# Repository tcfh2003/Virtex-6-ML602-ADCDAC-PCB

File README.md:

# ADC/DAC FPGA Mezannine Card utilizing VITA 57.1 compliant LPC connector.

ADC used is ADC10D040CIVS and has two 10-bit 40 MSa/s channels. DAC used is DAC5652 and has two 10-bit 200 MSa/s channels. 

You can view the PCB online by using https://kicanvas.org (made by theacodes, project github link https://github.com/theacodes/kicanvas.git), and providing the link for the .pro file in this repo.

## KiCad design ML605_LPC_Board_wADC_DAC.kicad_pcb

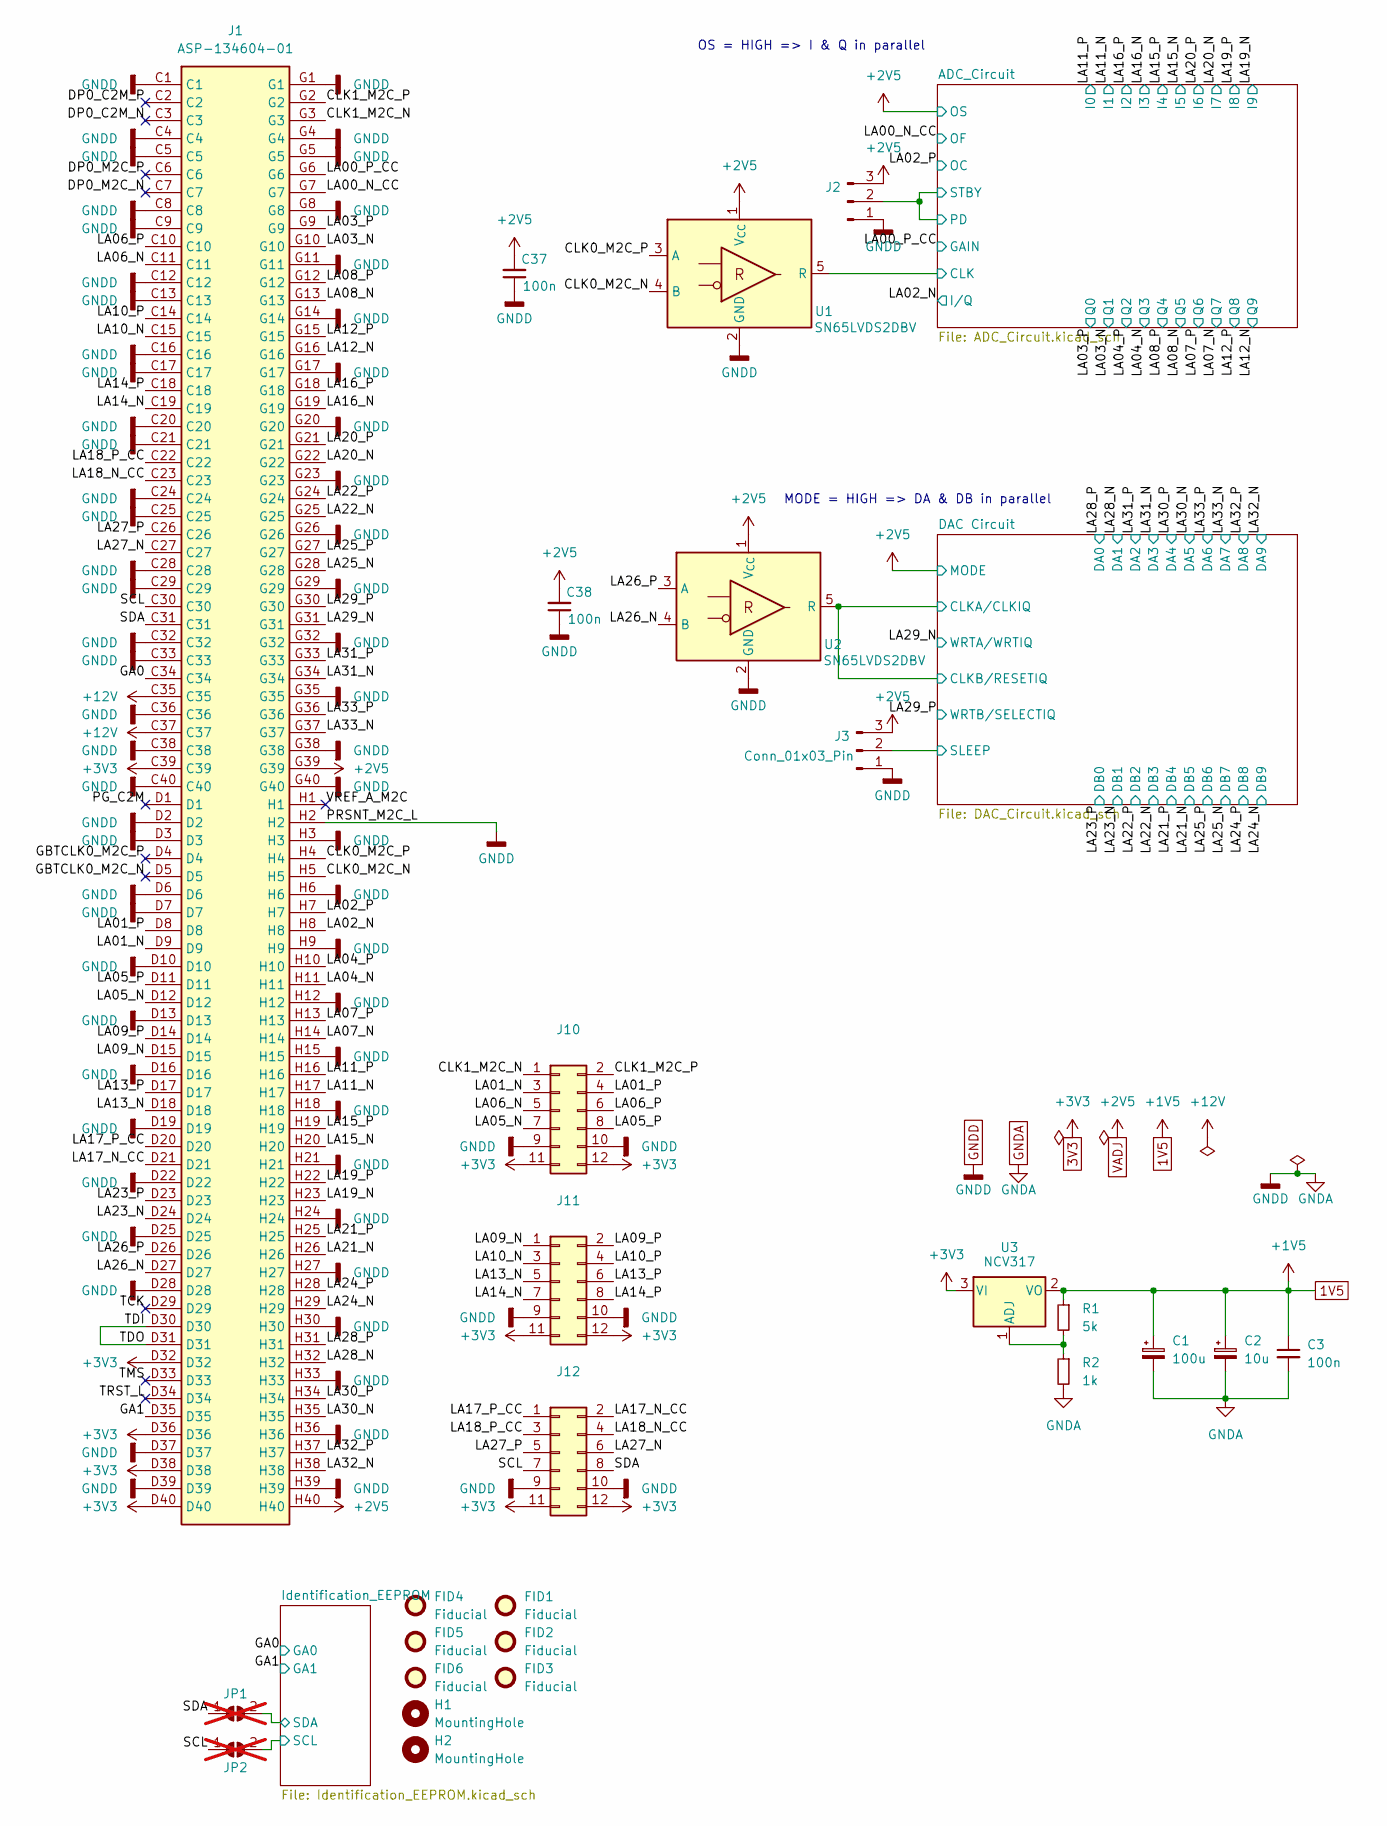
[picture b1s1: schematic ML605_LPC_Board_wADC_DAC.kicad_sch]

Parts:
C1: 100u; CP_Elec_5x5.3; LCSC C15008 (MLCC 1206)
C2: 10u; C_0805_2012Metric_Pad1.18x1.45mm_HandSolder; LCSC C408141
C3, C37, C38: 100n; C_0805_2012Metric_Pad1.18x1.45mm_HandSolder; LCSC C49678
FID1, FID2, FID3, FID4, FID5, FID6: Fiducial; Fiducial_0.5mm_Mask1mm; Mouser Link N/A
H1, H2: MountingHole; MountingHole_3.2mm_M3; Mouser Link N/A
J1: ASP-134604-01; ASP13460401; Mouser Part Number 200-ASP-134604-01
J2, J3: Conn_01x03_Pin; PinHeader_1x03_P2.54mm_Vertical_SMD_Pin1Left
J10, J11, J12: Conn_02x06_Odd_Even; PinSocket_2x06_P2.54mm_Vertical
JP1, JP2: SolderJumper_2_Open; SolderJumper-2_P1.3mm_Open_TrianglePad1.0x1.5mm; Mouser Link N/A; not fitted
R1: 5k; R_0805_2012Metric_Pad1.20x1.40mm_HandSolder
R2: 1k; R_0805_2012Metric_Pad1.20x1.40mm_HandSolder
U1, U2: SN65LVDS2DBV; SOT-23-5
U3: NCV317; SOT-223-3_TabPin2

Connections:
1V5: C1.1, C2.1, C3.1, R1.1, U3.2 (VO); also elsewhere on the board
3V3: J1.C39, J1.D32, J1.D36, J1.D38, J1.D40, J10.11, J10.12, J11.11, J11.12, J12.11, J12.12, U3.3 (VI); also elsewhere on the board
+12V: J1.C35, J1.C37
/ADC_Circuit/CLK: U1.5 (R); also elsewhere on the board
/ADC_Circuit/PD: J2.2; also elsewhere on the board
/CLK0_M2C_N: J1.H5, U1.4 (B)
/CLK0_M2C_P: J1.H4, U1.3 (A)
/CLK1_M2C_N: J1.G3, J10.1
/CLK1_M2C_P: J1.G2, J10.2
/DAC Circuit/CLKA/CLKIQ: U2.5 (R); also elsewhere on the board
/DAC Circuit/SLEEP: J3.2; also elsewhere on the board
/DP0_C2M_N: J1.C3
/DP0_C2M_P: J1.C2
/DP0_M2C_N: J1.C7
/DP0_M2C_P: J1.C6
/GA0: J1.C34; also elsewhere on the board
/GA1: J1.D35; also elsewhere on the board
/GBTCLK0_M2C_N: J1.D5
/GBTCLK0_M2C_P: J1.D4
/Identification_EEPROM/SCL: JP2.2 (B); also elsewhere on the board
/Identification_EEPROM/SDA: JP1.2 (B); also elsewhere on the board
/LA00_N_CC: J1.G7; also elsewhere on the board
/LA00_P_CC: J1.G6; also elsewhere on the board
/LA01_N: J1.D9, J10.3
/LA01_P: J1.D8, J10.4
/LA02_N: J1.H8; also elsewhere on the board
/LA02_P: J1.H7; also elsewhere on the board
/LA03_N: J1.G10; also elsewhere on the board
/LA03_P: J1.G9; also elsewhere on the board
/LA04_N: J1.H11; also elsewhere on the board
/LA04_P: J1.H10; also elsewhere on the board
/LA05_N: J1.D12, J10.7
/LA05_P: J1.D11, J10.8
/LA06_N: J1.C11, J10.5
/LA06_P: J1.C10, J10.6
/LA07_N: J1.H14; also elsewhere on the board
/LA07_P: J1.H13; also elsewhere on the board
/LA08_N: J1.G13; also elsewhere on the board
/LA08_P: J1.G12; also elsewhere on the board
/LA09_N: J1.D15, J11.1
/LA09_P: J1.D14, J11.2
/LA10_N: J1.C15, J11.3
/LA10_P: J1.C14, J11.4
/LA11_N: J1.H17; also elsewhere on the board
/LA11_P: J1.H16; also elsewhere on the board
/LA12_N: J1.G16; also elsewhere on the board
/LA12_P: J1.G15; also elsewhere on the board
/LA13_N: J1.D18, J11.5
/LA13_P: J1.D17, J11.6
/LA14_N: J1.C19, J11.7
/LA14_P: J1.C18, J11.8
/LA15_N: J1.H20; also elsewhere on the board
/LA15_P: J1.H19; also elsewhere on the board
/LA16_N: J1.G19; also elsewhere on the board
/LA16_P: J1.G18; also elsewhere on the board
/LA17_N_CC: J1.D21, J12.2
/LA17_P_CC: J1.D20, J12.1
/LA18_N_CC: J1.C23, J12.4
/LA18_P_CC: J1.C22, J12.3
/LA19_N: J1.H23; also elsewhere on the board
/LA19_P: J1.H22; also elsewhere on the board
/LA20_N: J1.G22; also elsewhere on the board
/LA20_P: J1.G21; also elsewhere on the board
/LA21_N: J1.H26; also elsewhere on the board
/LA21_P: J1.H25; also elsewhere on the board
/LA22_N: J1.G25; also elsewhere on the board
/LA22_P: J1.G24; also elsewhere on the board
/LA23_N: J1.D24; also elsewhere on the board
/LA23_P: J1.D23; also elsewhere on the board
/LA24_N: J1.H29; also elsewhere on the board
/LA24_P: J1.H28; also elsewhere on the board
/LA25_N: J1.G28; also elsewhere on the board
/LA25_P: J1.G27; also elsewhere on the board
/LA26_N: J1.D27, U2.4 (B)
/LA26_P: J1.D26, U2.3 (A)
/LA27_N: J1.C27, J12.6
/LA27_P: J1.C26, J12.5
/LA28_N: J1.H32; also elsewhere on the board
/LA28_P: J1.H31; also elsewhere on the board
/LA29_N: J1.G31; also elsewhere on the board
/LA29_P: J1.G30; also elsewhere on the board
/LA30_N: J1.H35; also elsewhere on the board
/LA30_P: J1.H34; also elsewhere on the board
/LA31_N: J1.G34; also elsewhere on the board
/LA31_P: J1.G33; also elsewhere on the board
/LA32_N: J1.H38; also elsewhere on the board
/LA32_P: J1.H37; also elsewhere on the board
/LA33_N: J1.G37; also elsewhere on the board
/LA33_P: J1.G36; also elsewhere on the board
/PG_C2M: J1.D1
/SCL: J1.C30, J12.7, JP2.1 (A)
/SDA: J1.C31, J12.8, JP1.1 (A)
/TCK: J1.D29
/TDI: J1.D30, J1.D31
/TMS: J1.D33
/TRST_L: J1.D34
/VREF_A_M2C: J1.H1
GNDA: C1.2, C2.2, C3.2, C37.1, C38.1, J1.C1, J1.C4, J1.C5, J1.C8, J1.C9, J1.C12, J1.C13, J1.C16, J1.C17, J1.C20, J1.C21, J1.C24, J1.C25, J1.C28, J1.C29, J1.C32, J1.C33, J1.C36, J1.C38, J1.C40, J1.D2, J1.D3, J1.D6, J1.D7, J1.D10, J1.D13, J1.D16, J1.D19, J1.D22, J1.D25, J1.D28, J1.D37, J1.D39, J1.G1, J1.G4, J1.G5, J1.G8, J1.G11, J1.G14, J1.G17, J1.G20, J1.G23, J1.G26, J1.G29, J1.G32, J1.G35, J1.G38, J1.G40, J1.H2, J1.H3, J1.H6, J1.H9, J1.H12, J1.H15, J1.H18, J1.H21, J1.H24, J1.H27, J1.H30, J1.H33, J1.H36, J1.H39, J2.1, J3.1, J10.9, J10.10, J11.9, J11.10, J12.9, J12.10, R2.2, U1.2 (GND), U2.2 (GND); also elsewhere on the board
unnamed: R1.2, R2.1, U3.1 (ADJ)
VADJ: C37.2, C38.2, J1.G39, J1.H40, J2.3, J3.3, U1.1 (V_{CC}), U2.1 (V_{CC}); also elsewhere on the board

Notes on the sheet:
OS = HIGH => I & Q in parallel
MODE = HIGH => DA & DB in parallel

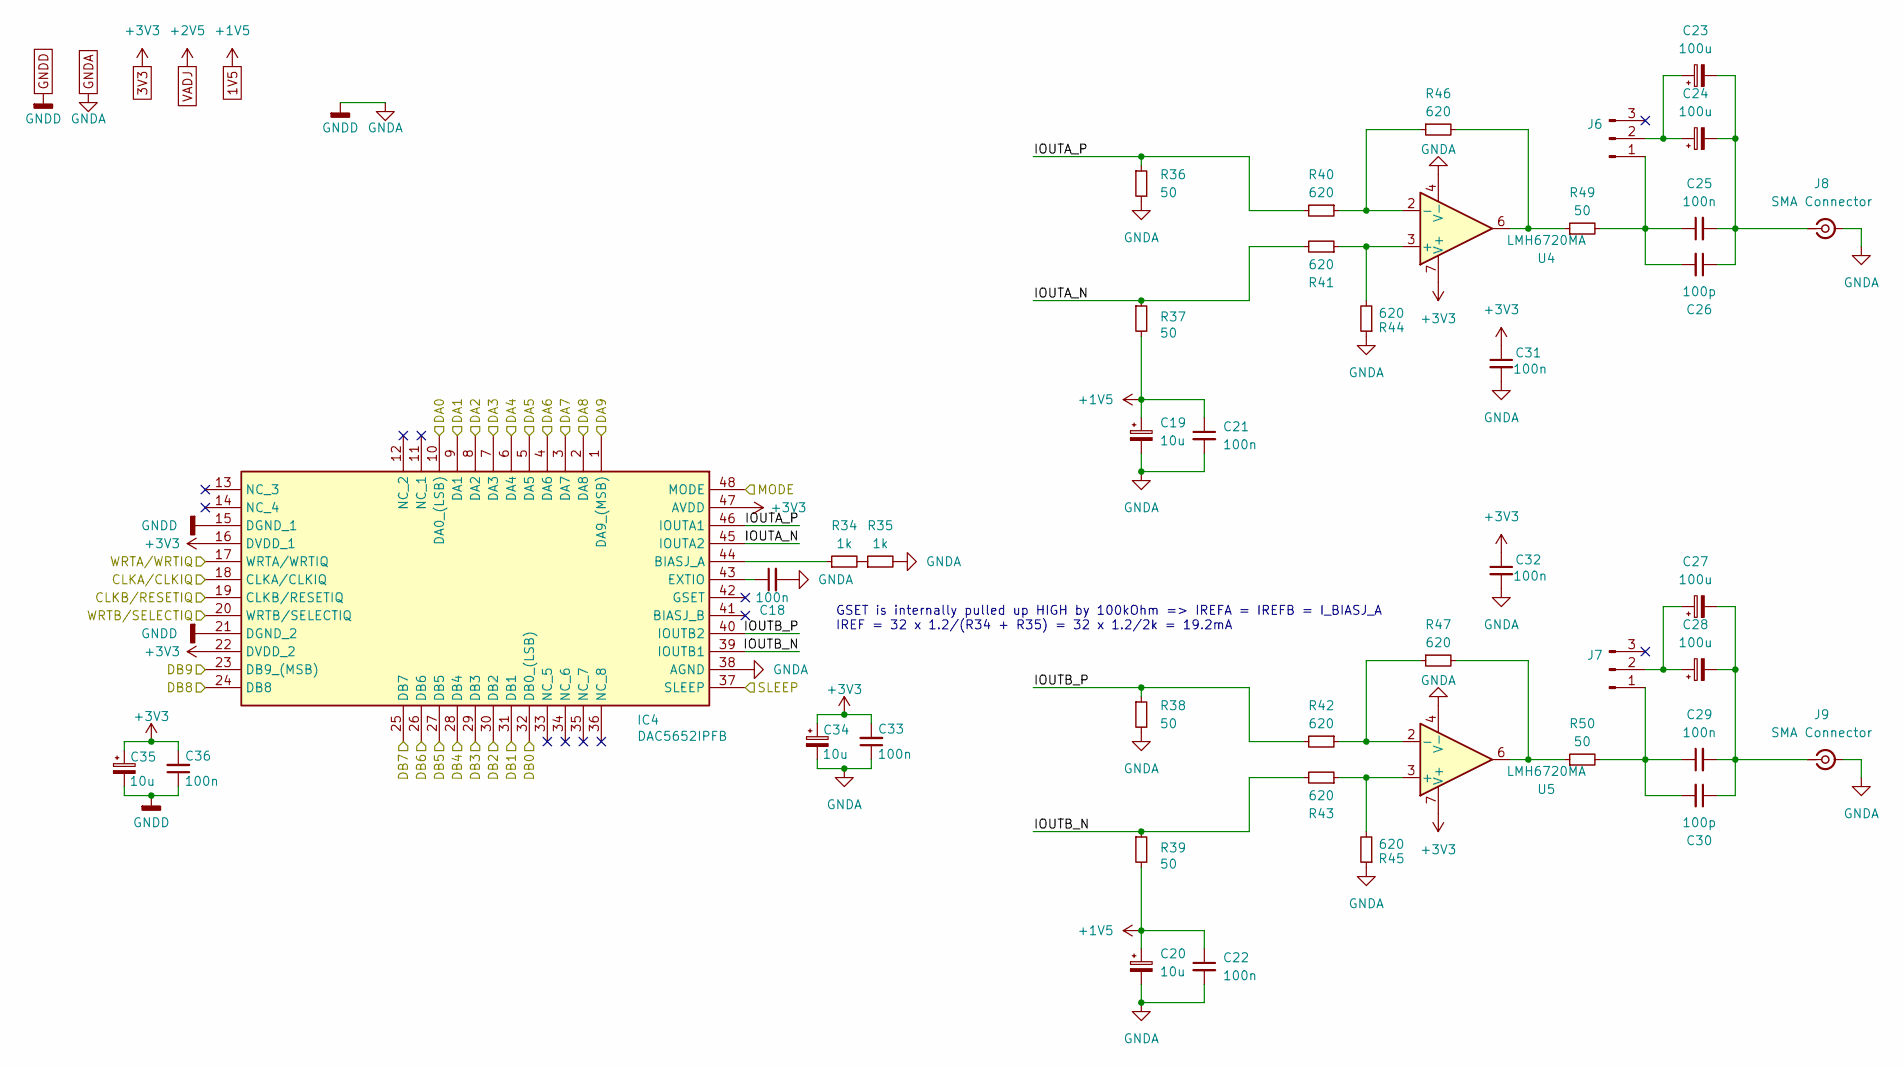
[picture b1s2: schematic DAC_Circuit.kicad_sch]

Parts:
C18, C21, C22, C25, C29, C31, C32, C33, C36: 100n; C_0805_2012Metric_Pad1.18x1.45mm_HandSolder; LCSC C49678
C19, C20, C34, C35: 10u; C_0805_2012Metric_Pad1.18x1.45mm_HandSolder; LCSC C408141
C23, C24, C27, C28: 100u; CP_Elec_5x5.3; LCSC C15008 (MLCC 1206)
C26, C30: 100p; C_0805_2012Metric_Pad1.18x1.45mm_HandSolder; LCSC C1790
IC4: DAC5652IPFB; TQFP-48_7x7mm_P0.5mm; Mouser Part Number 595-DAC5652IPFB
J6, J7: Conn_01x03_Pin; PinHeader_1x03_P2.54mm_Vertical_SMD_Pin1Left
J8, J9: SMA Connector; SMA_Amphenol_132134_Vertical
R34, R35: 1k; R_0805_2012Metric_Pad1.20x1.40mm_HandSolder
R36, R37, R38, R39, R49, R50: 50; R_0805_2012Metric_Pad1.20x1.40mm_HandSolder
R40, R41, R42, R43, R44, R45, R46, R47: 620; R_0805_2012Metric_Pad1.20x1.40mm_HandSolder
U4, U5: LMH6720MA; SOIC-8_3.9x4.9mm_P1.27mm

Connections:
1V5: C19.1, C20.1, C21.1, C22.1, R37.2, R39.2; also elsewhere on the board
3V3: C31.1, C32.1, C33.2, C34.1, C35.1, C36.2, IC4.16 (DVDD_1), IC4.22 (DVDD_2), IC4.47 (AVDD), U4.7 (V+), U5.7 (V+); also elsewhere on the board
/DAC Circuit/CLKA/CLKIQ: IC4.18 (CLKA/CLKIQ), IC4.19 (CLKB/RESETIQ); also elsewhere on the board
/DAC Circuit/IOUTA_N: IC4.45 (IOUTA2), R37.1, R41.2
/DAC Circuit/IOUTA_P: IC4.46 (IOUTA1), R36.1, R40.2
/DAC Circuit/IOUTB_N: IC4.39 (IOUTB1), R39.1, R43.2
/DAC Circuit/IOUTB_P: IC4.40 (IOUTB2), R38.1, R42.2
/DAC Circuit/SLEEP: IC4.37 (SLEEP); also elsewhere on the board
/LA21_N: IC4.27 (DB5); also elsewhere on the board
/LA21_P: IC4.28 (DB4); also elsewhere on the board
/LA22_N: IC4.29 (DB3); also elsewhere on the board
/LA22_P: IC4.30 (DB2); also elsewhere on the board
/LA23_N: IC4.31 (DB1); also elsewhere on the board
/LA23_P: IC4.32 (DB0_(LSB)); also elsewhere on the board
/LA24_N: IC4.23 (DB9_(MSB)); also elsewhere on the board
/LA24_P: IC4.24 (DB8); also elsewhere on the board
/LA25_N: IC4.25 (DB7); also elsewhere on the board
/LA25_P: IC4.26 (DB6); also elsewhere on the board
/LA28_N: IC4.9 (DA1); also elsewhere on the board
/LA28_P: IC4.10 (DA0_(LSB)); also elsewhere on the board
/LA29_N: IC4.17 (WRTA/WRTIQ); also elsewhere on the board
/LA29_P: IC4.20 (WRTB/SELECTIQ); also elsewhere on the board
/LA30_N: IC4.5 (DA5); also elsewhere on the board
/LA30_P: IC4.6 (DA4); also elsewhere on the board
/LA31_N: IC4.7 (DA3); also elsewhere on the board
/LA31_P: IC4.8 (DA2); also elsewhere on the board
/LA32_N: IC4.1 (DA9_(MSB)); also elsewhere on the board
/LA32_P: IC4.2 (DA8); also elsewhere on the board
/LA33_N: IC4.3 (DA7); also elsewhere on the board
/LA33_P: IC4.4 (DA6); also elsewhere on the board
GNDA: C18.2, C19.2, C20.2, C21.2, C22.2, C31.2, C32.2, C33.1, C34.2, C35.2, C36.1, IC4.15 (DGND_1), IC4.21 (DGND_2), IC4.38 (AGND), J8.2 (Ext), J9.2 (Ext), R35.2, R36.2, R38.2, R44.1, R45.1, U4.4 (V-), U5.4 (V-); also elsewhere on the board
unnamed: IC4.44 (BIASJ_A), R34.1
unnamed: C18.1, IC4.43 (EXTIO)
unnamed: C25.1, C26.2, J6.1, R49.2
unnamed: C23.1, C24.1, J6.2
unnamed: C29.1, C30.2, J7.1, R50.2
unnamed: C27.1, C28.1, J7.2
unnamed: C23.2, C24.2, C25.2, C26.1, J8.1 (In)
unnamed: C27.2, C28.2, C29.2, C30.1, J9.1 (In)
unnamed: R34.2, R35.1
unnamed: R46.2, R49.1, U4.6
unnamed: R47.2, R50.1, U5.6
unnamed: R41.1, R44.2, U4.3 (+)
unnamed: R40.1, R46.1, U4.2 (-)
unnamed: R43.1, R45.2, U5.3 (+)
unnamed: R42.1, R47.1, U5.2 (-)
VADJ: IC4.48 (MODE); also elsewhere on the board

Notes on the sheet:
GSET is internally pulled up HIGH by 100kOhm => IREFA = IREFB = I_BIASJ_A IREF = 32 x 1.2/(R34 + R35) = 32 x 1.2/2k = 19.2mA

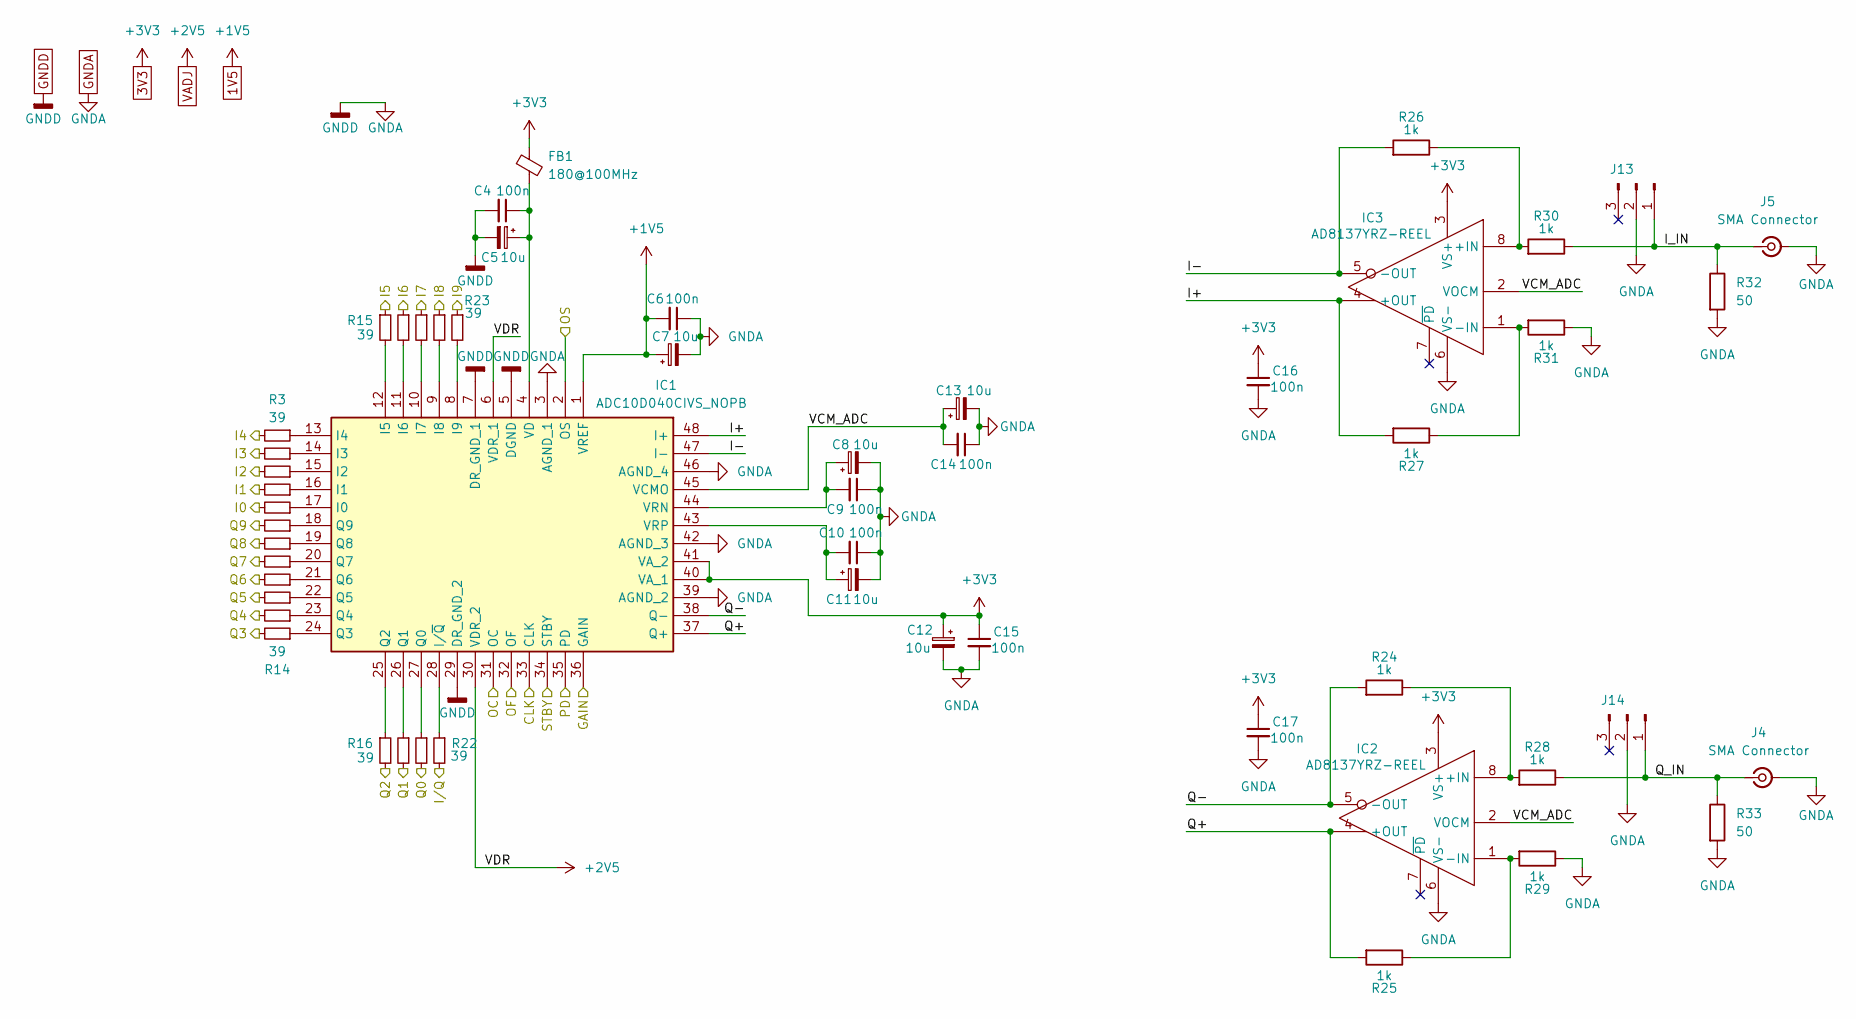
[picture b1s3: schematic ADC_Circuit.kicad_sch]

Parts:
C4, C6, C9, C10, C14, C15, C16, C17: 100n; C_0805_2012Metric_Pad1.18x1.45mm_HandSolder; LCSC C49678
C5, C7, C8, C11, C12, C13: 10u; C_0805_2012Metric_Pad1.18x1.45mm_HandSolder; LCSC C408141
FB1: 180@100MHz; L_0805_2012Metric_Pad1.15x1.40mm_HandSolder
IC1: ADC10D040CIVS_NOPB; TQFP-48_7x7mm_P0.5mm; Mouser Part Number 926-ADC10D040CIVSNPB
IC2, IC3: AD8137YRZ-REEL; SOIC-8_3.9x4.9mm_P1.27mm; Mouser Part Number 584-AD8137YRZ-R
J4, J5: SMA Connector; SMA_Amphenol_132134_Vertical
J13, J14: Conn_01x03_Pin; PinHeader_1x03_P2.54mm_Vertical_SMD_Pin1Left
R3, R4, R5, R6, R7, R8, R9, R10, R11, R12, R13, R14, R15, R16, R17, R18, R19, R20, R21, R22, R23: 39; R_0805_2012Metric_Pad1.20x1.40mm_HandSolder
R24, R25, R26, R27, R28, R29, R30, R31: 1k; R_0805_2012Metric_Pad1.20x1.40mm_HandSolder
R32, R33: 50; R_0805_2012Metric_Pad1.20x1.40mm_HandSolder

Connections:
1V5: C6.2, C7.1, IC1.1 (VREF); also elsewhere on the board
3V3: C12.1, C15.1, C16.1, C17.1, FB1.1, IC1.40 (VA_1), IC1.41 (VA_2), IC2.3 (VS+), IC3.3 (VS+); also elsewhere on the board
/ADC_Circuit/CLK: IC1.33 (CLK); also elsewhere on the board
/ADC_Circuit/I+: IC1.48 (I+), IC3.4 (+OUT), R27.2
/ADC_Circuit/I-: IC1.47 (I-), IC3.5 (-OUT), R26.2
/ADC_Circuit/I_IN: J5.1 (In), J13.1, R30.1, R32.1
/ADC_Circuit/PD: IC1.34 (STBY), IC1.35 (PD); also elsewhere on the board
/ADC_Circuit/Q+: IC1.37 (Q+), IC2.4 (+OUT), R25.2
/ADC_Circuit/Q-: IC1.38 (Q-), IC2.5 (-OUT), R24.2
/ADC_Circuit/Q_IN: J4.1 (In), J14.1, R28.1, R33.1
/ADC_Circuit/VCM_ADC: C13.1, C14.2, IC1.45 (VCMO), IC2.2 (VOCM), IC3.2 (VOCM)
/LA00_N_CC: IC1.32 (OF); also elsewhere on the board
/LA00_P_CC: IC1.36 (GAIN); also elsewhere on the board
/LA02_N: R22.2; also elsewhere on the board
/LA02_P: IC1.31 (OC); also elsewhere on the board
/LA03_N: R18.2; also elsewhere on the board
/LA03_P: R20.2; also elsewhere on the board
/LA04_N: R14.2; also elsewhere on the board
/LA04_P: R16.2; also elsewhere on the board
/LA07_N: R10.2; also elsewhere on the board
/LA07_P: R11.2; also elsewhere on the board
/LA08_N: R12.2; also elsewhere on the board
/LA08_P: R13.2; also elsewhere on the board
/LA11_N: R6.2; also elsewhere on the board
/LA11_P: R7.2; also elsewhere on the board
/LA12_N: R8.2; also elsewhere on the board
/LA12_P: R9.2; also elsewhere on the board
/LA15_N: R15.1; also elsewhere on the board
/LA15_P: R3.2; also elsewhere on the board
/LA16_N: R4.2; also elsewhere on the board
/LA16_P: R5.2; also elsewhere on the board
/LA19_N: R23.1; also elsewhere on the board
/LA19_P: R21.1; also elsewhere on the board
/LA20_N: R19.1; also elsewhere on the board
/LA20_P: R17.1; also elsewhere on the board
GNDA: C4.2, C5.2, C6.1, C7.2, C8.2, C9.1, C10.1, C11.2, C12.2, C13.2, C14.1, C15.2, C16.2, C17.2, IC1.3 (AGND_1), IC1.5 (DGND), IC1.7 (DR_GND_1), IC1.29 (DR_GND_2), IC1.39 (AGND_2), IC1.42 (AGND_3), IC1.46 (AGND_4), IC2.6 (VS-), IC3.6 (VS-), J4.2 (Ext), J5.2 (Ext), J13.2, J14.2, R29.1, R31.1, R32.2, R33.2; also elsewhere on the board
unnamed: IC1.17 (I0), R7.1
unnamed: IC1.16 (I1), R6.1
unnamed: IC1.15 (I2), R5.1
unnamed: IC1.14 (I3), R4.1
unnamed: IC1.13 (I4), R3.1
unnamed: IC1.12 (I5), R15.2
unnamed: IC1.11 (I6), R17.2
unnamed: IC1.10 (I7), R19.2
unnamed: IC1.9 (I8), R21.2
unnamed: IC1.8 (I9), R23.2
unnamed: IC1.28 (I/~Q), R22.1
unnamed: IC1.27 (Q0), R20.1
unnamed: IC1.26 (Q1), R18.1
unnamed: IC1.25 (Q2), R16.1
unnamed: IC1.24 (Q3), R14.1
unnamed: IC1.23 (Q4), R13.1
unnamed: IC1.22 (Q5), R12.1
unnamed: IC1.21 (Q6), R11.1
unnamed: IC1.20 (Q7), R10.1
unnamed: IC1.19 (Q8), R9.1
unnamed: IC1.18 (Q9), R8.1
unnamed: C4.1, C5.1, FB1.2, IC1.4 (VD)
unnamed: C8.1, C9.2, IC1.44 (VRN)
unnamed: C10.2, C11.1, IC1.43 (VRP)
unnamed: IC2.8 (+IN), R24.1, R28.2
unnamed: IC2.1 (-IN), R25.1, R29.2
unnamed: IC3.8 (+IN), R26.1, R30.2
unnamed: IC3.1 (-IN), R27.1, R31.2
VADJ: IC1.2 (OS), IC1.6 (VDR_1), IC1.30 (VDR_2); also elsewhere on the board

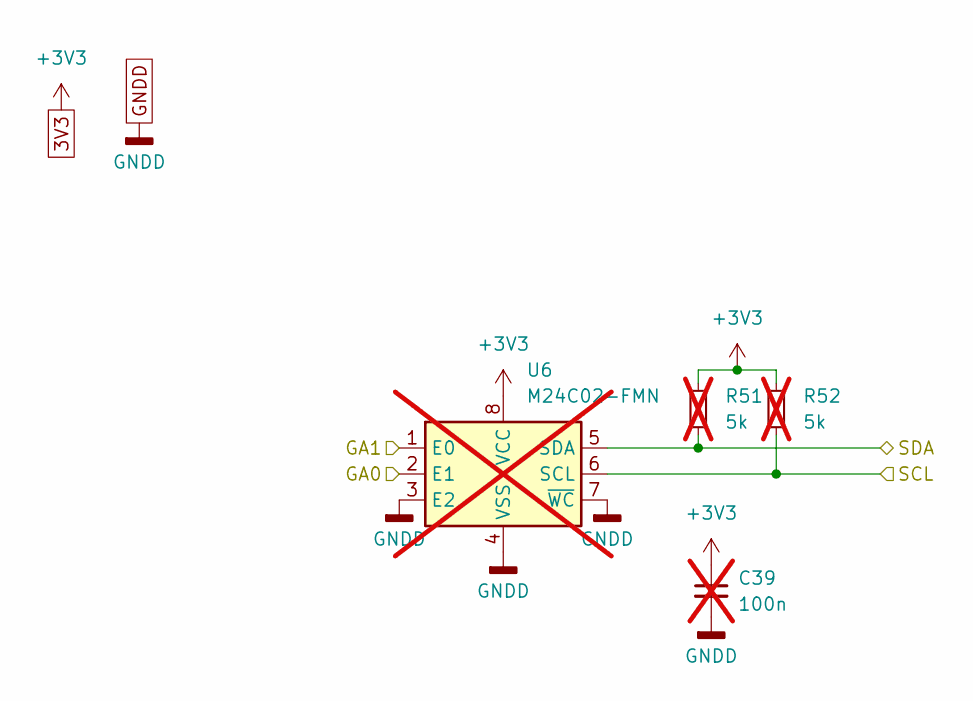
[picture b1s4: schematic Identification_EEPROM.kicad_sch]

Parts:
C39: 100n; C_0805_2012Metric_Pad1.18x1.45mm_HandSolder; not fitted
R51, R52: 5k; R_0805_2012Metric_Pad1.20x1.40mm_HandSolder; not fitted
U6: M24C02-FMN; SOIC-8_3.9x4.9mm_P1.27mm; not fitted

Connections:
3V3: C39.1, R51.1, R52.1, U6.8 (VCC); also elsewhere on the board
/GA0: U6.2 (E1); also elsewhere on the board
/GA1: U6.1 (E0); also elsewhere on the board
/Identification_EEPROM/SCL: R52.2, U6.6 (SCL); also elsewhere on the board
/Identification_EEPROM/SDA: R51.2, U6.5 (SDA); also elsewhere on the board
GNDA: C39.2, U6.3 (E2), U6.4 (VSS), U6.7 (~WC); also elsewhere on the board

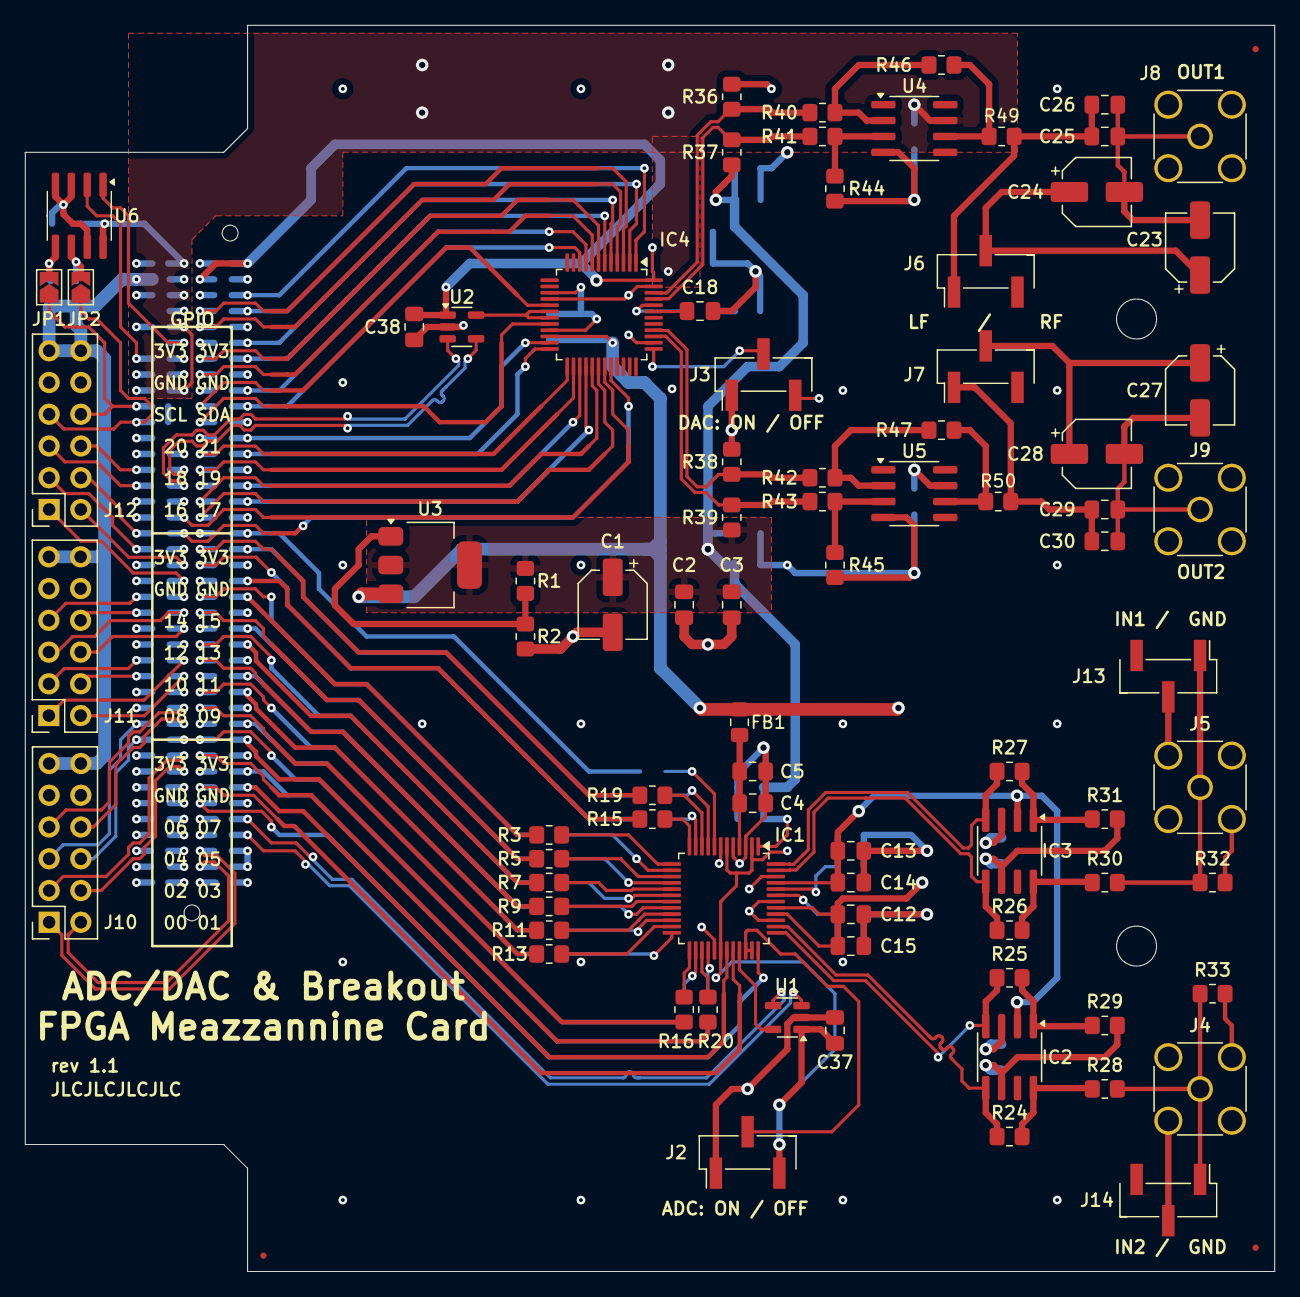
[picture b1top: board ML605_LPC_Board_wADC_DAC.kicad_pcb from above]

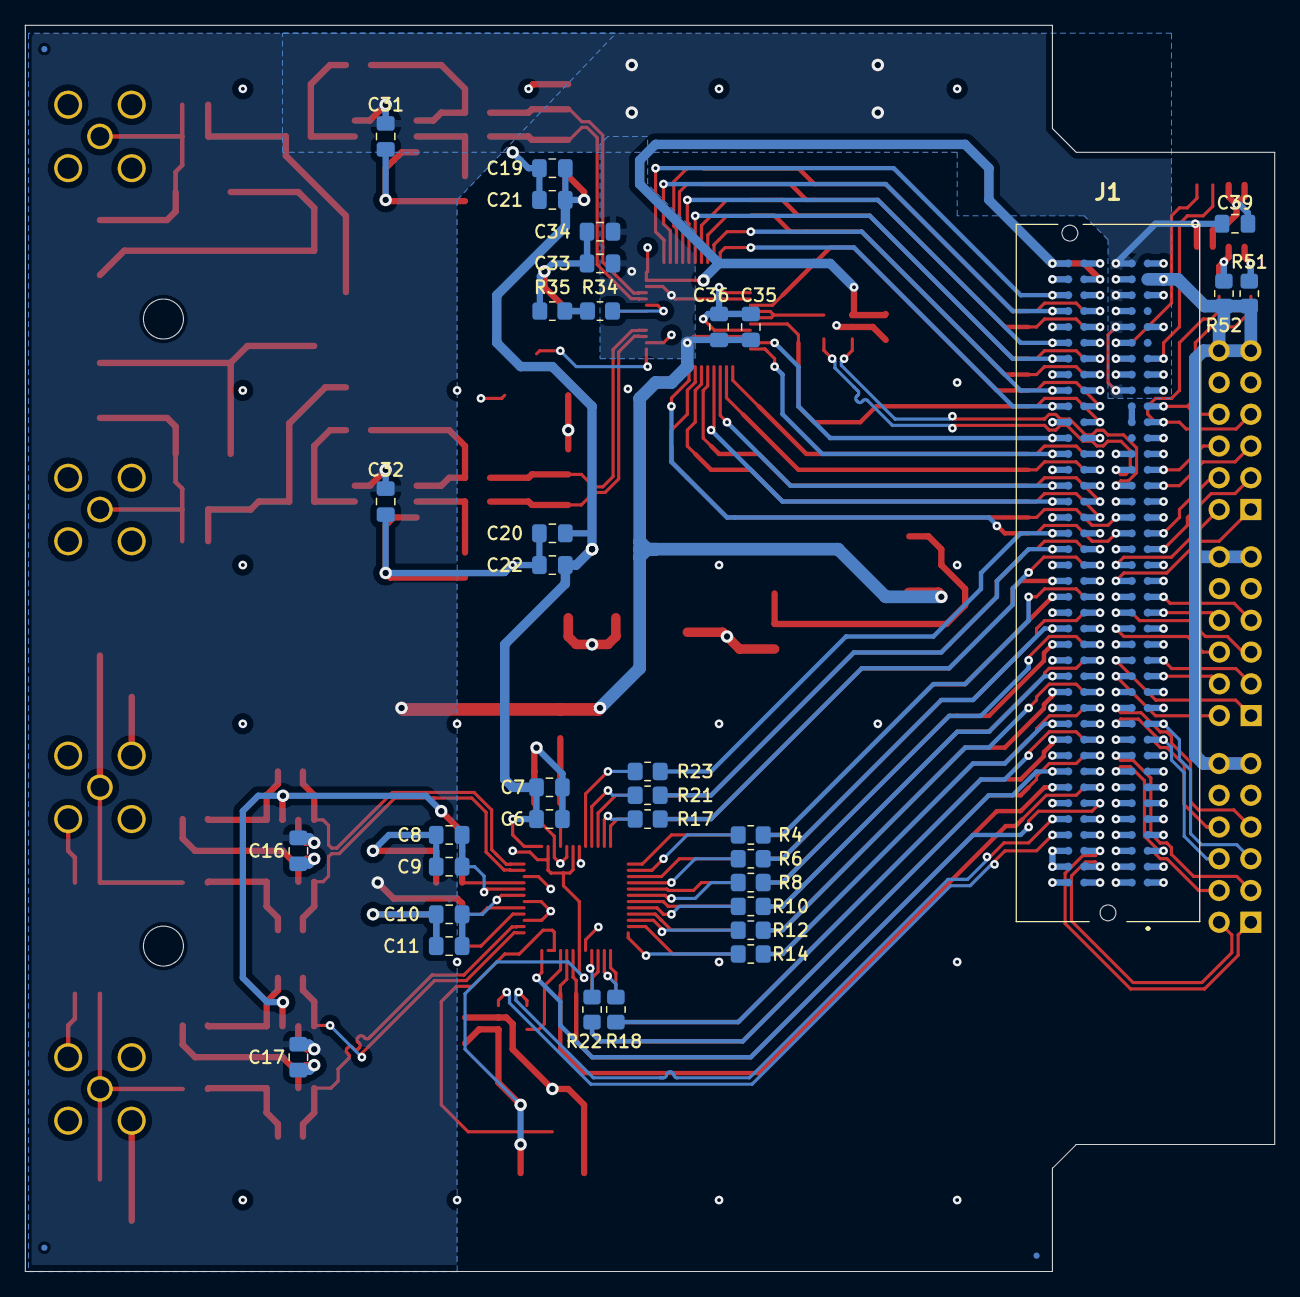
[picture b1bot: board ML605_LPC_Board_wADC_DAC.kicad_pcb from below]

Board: 4 copper layers, 99.9 x 99.7 mm, 125 parts (38 on the bottom side), 143 nets.

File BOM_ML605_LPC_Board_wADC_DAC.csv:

Reference,Value,Datasheet,Footprint,Mouser Link,LCSC,Qty,DNP,Mouser Code,Mouser Unit Price,Mouser Total Price
"C1,C23,C24,C27,C28",100u,~,Capacitor_SMD:CP_Elec_5x5.3,https://ro.mouser.com/ProductDetail/Wurth-Elektronik/8650801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,C15008 (MLCC 1206),5,,710-865080142007 ,0.693,6.93
"C2,C5,C7,C8,C11,C12,C13,C19,C20,C34,C35",10u,~,Capacitor_SMD:C_0805_2012Metric_Pad1.18x1.45mm_HandSolder,https://ro.mouser.com/ProductDetail/Samsung-Electro-Mechanic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,C408141,11,,187-CL21A106KOQNNNE ,0.178,2.67
"C3,C4,C6,C9,C10,C14,C15,C16,C17,C18,C21,C22,C25,C29,C31,C32,C33,C36,C37,C38",100n,~,Capacitor_SMD:C_0805_2012Metric_Pad1.18x1.45mm_HandSolder,https://ro.mouser.com/ProductDetail/KEMET/C0805C104Z5VACTU?q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,C49678,20,,80-C0805C104Z5V ,0.109,2.725
"C26,C30",100p,~,Capacitor_SMD:C_0805_2012Metric_Pad1.18x1.45mm_HandSolder,https://ro.mouser.com/ProductDetail/Wurth-Elektronik/8850120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,C1790,2,,710-885012007034 ,0.46,0.92
"U4,U5",LMH6702MA,http://www.ti.com/lit/ds/symlink/lmh6702.pdf,Package_SO:SOIC-8_3.9x4.9mm_P1.27mm,https://ro.mouser.com/ProductDetail/Texas-Instruments/LMH672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,,2,,926-LMH6720MA/NOPB ,10.54,21.08
U3,NCV317,http://www.ti.com/lit/ds/symlink/lm317.pdf,Package_TO_SOT_SMD:SOT-223-3_TabPin2,https://ro.mouser.com/ProductDetail/onsemi/NCV317MBSTT3G?qs=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,,1,,863-NCV317MBSTT3G ,1.98,1.98
"U1,U2",LMV7219M7,https://www.ti.com/lit/ds/symlink/lmv7219.pdf,Package_TO_SOT_SMD:SOT-353_SC-70-5,https://ro.mouser.com/ProductDetail/Texas-Instruments/LMV721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,,2,,926-LMV7219M5X/NOPB ,11.78,23.56
"R40,R41,R42,R43,R44,R45,R46,R47",620,~,Resistor_SMD:R_0805_2012Metric_Pad1.20x1.40mm_HandSolder,https://ro.mouser.com/ProductDetail/Kamaya/RMC1-10-621JTP?qs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,,8,,791-RMC1/10-621JTP ,0.084,0.84
"R32,R33,R36,R37,R38,R39",50,~,Resistor_SMD:R_0805_2012Metric_Pad1.20x1.40mm_HandSolder,https://ro.mouser.com/ProductDetail/Vishay-Dale/CRCW080550R0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,,6,,71-CRCW0805-50 ,0.941,9.41
"R3,R4,R5,R6,R7,R8,R9,R10,R11,R12,R13,R14,R15,R16,R17,R18,R19,R20,R21,R22,R23",39,~,Resistor_SMD:R_0805_2012Metric_Pad1.20x1.40mm_HandSolder,https://ro.mouser.com/ProductDetail/Susumu/RR1220Q-39R2-D-M?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,,21,,754-RR1220Q-39R2D-M ,0.262,6.55
"R2,R24,R25,R26,R27,R28,R29,R30,R31,R34,R35,R48",1k,~,Resistor_SMD:R_0805_2012Metric_Pad1.20x1.40mm_HandSolder,https://ro.mouser.com/ProductDetail/YAGEO/AC0805JR-071KL?qs=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,,12,,603-AC0805JR-071KL ,0.079,1.185
R1,5k,~,Resistor_SMD:R_0805_2012Metric_Pad1.20x1.40mm_HandSolder,https://ro.mouser.com/ProductDetail/SEI-Stackpole/RMCF0805FT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,,1,,708-RMCF0805FT4K99 ,0.46,0.46
L1,100u,~,Inductor_SMD:L_0805_2012Metric_Pad1.05x1.20mm_HandSolder,https://ro.mouser.com/ProductDetail/TAIYO-YUDEN/LBR2012T101K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,,1,,963-LBR2012T101K ,0.46,0.46
"JP1,JP2",SolderJumper_2_Open,~,Jumper:SolderJumper-2_P1.3mm_Open_TrianglePad1.0x1.5mm,N/A,,2,DNP,,,0
"J10,J11,J12",Conn_02x06_Odd_Even,~,Connector_PinSocket_2.54mm:PinSocket_2x06_P2.54mm_Vertical,https://ro.mouser.com/ProductDetail/Samtec/SSW-106-01-T-D?qs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,,3,,200-SSW10601TD ,5.59,16.77
"J4,J5,J8,J9",SMA Connector,~,Connector_Coaxial:SMA_Amphenol_132134_Vertical,https://ro.mouser.com/ProductDetail/LPRS/SMA-CONNECTOR?qs=j%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,,4,,471-SMACONNECTOR ,8.51,34.04
"J2,J3,J6,J7,J13,J14",Conn_01x03_Pin,~,Connector_PinHeader_2.54mm:PinHeader_1x03_P2.54mm_Vertical_SMD_Pin1Left,https://ro.mouser.com/ProductDetail/Amphenol-FCI/10129380-90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,,6,,649-1012938090301BLF ,0.371,3.71
J1,ASP-134604-01,https://componentsearchengine.com/Datasheets/2/ASP-134604-01.pdf,ASP13460401,https://ro.mouser.com/ProductDetail/Samtec/ASP-134604-01?qs=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,,1,,200-ASP-134604-01 ,95.73,95.73
IC4,DAC5652IPFB,http://www.ti.com/lit/gpn/dac5652,Package_QFP:TQFP-48_7x7mm_P0.5mm,https://ro.mouser.com/ProductDetail/Texas-Instruments/DAC565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,,1,,595-DAC5652IPFB ,62.27,62.27
"IC2,IC3",AD8137YRZ-REEL,https://www.arrow.com/en/products/ad8137yrz-reel/analog-devices,Package_SO:SOIC-8_3.9x4.9mm_P1.27mm,https://ro.mouser.com/ProductDetail/Analog-Devices/AD8137YRZ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,,2,,584-AD8137YRZ-R ,15.39,30.78
IC1,ADC10D040CIVS_NOPB,http://www.ti.com/lit/gpn/adc10d040,Package_QFP:TQFP-48_7x7mm_P0.5mm,https://ro.mouser.com/ProductDetail/Texas-Instruments/ADC10D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,,1,,926-ADC10D040CIVSNPB ,63.36,63.36
,,,,,,,,,,
,,,,,,,,,,
,,,,,,,,,TOTAL PRICE (no VAT) :,385.43
,,,,,,,,,VAT (in Czech Republic):,21%
,,,,,,,,,,
,,,,,,,,,TOTAL PRICE (with VAT):,466.3703

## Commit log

2024-08-25 First Commit - 70% done
2024-08-26 Second commit, routed digital data inputs of DAC
    Now I have problems routing the WRTA & WRTB pins of the DAC. Will probably have to reassign some pins of the digital data inputs (potential solution: I could make the WRTA/WRTB pair be situated at LA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
2024-08-26 The ADC/DAC part of the board is done
    Now I just need to figure out how to do the GPIO breakout, but I have a lot more flexibility here. Ideally, I'd like to keep the PMOD connector format, however I'm not sure if that is going to be pos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
2024-08-26 Routing is done
    Routing is finally done! Now I just need to add some silkscreen markings, maybe a label, order number placement, and I need to place some ground stitching vias here and there
2024-08-26 Minor tracing mistakes fixed
2024-08-26 Other minor changes
    Including removing some unused nets in the schematic, changing L01_P/N back to L01_P/N_CC and adding the Mouser link to the BRD_PRSNT pullup resistor.
2024-08-29 Added some silkscreen markings
2024-08-29 Changed the VADJ vias to be 0.3mm/0.6mm
2024-08-29 Added GND stitching vias and fiducial markings
2024-08-30 Changed all via sizes to comply with the 0.2mm annular ring constraint
    And fixed some other issues regarding clearance constraints
2024-08-30 Fixed some minor silkscreen issues, added a missing capacitor connection
2024-08-30 Added fiducials on the back side of the PCB
2024-08-30 Moved J1 silkscreen reference designator
2024-08-30 New gerbers
2024-08-30 Increased trace width of ADC differential amplifier bypass capacitors
2024-08-30 Moved a grounding via
2024-08-30 Swapped INx / GND silkscreen markings in the ADC selection jumpers
2024-08-30 Thickened a GND trace for J10
2024-08-30 Added BOM
2024-08-30 Did some length matching for the ADC clock differential pair
2024-08-31 Review photos and Mezzaninne spelling mistake fixed
2024-08-31 Error in schematic, DAC output opamp is LMH6720, not LMH6702
2024-08-31 Rev 1.1
    Multiple changes are made, as per suggestions made by the redditors of r/PrintedCircuitBoards. Firstly, two 50 ohm resistors were added in series with the DAC output in order to comply with the minim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
    Some other things to look into are the use of some ferrite beads for supplies of the analog ICs.
2024-08-31 Updated BOM
2024-08-31 Reduced horizontal board dimension a bit
2024-08-31 Removed some 90 internal bends in the board outline for aesthetic purposes
2024-08-31 Fixed pcb dimensions (again)
2024-09-01 Added identification EEPROM to comply with the 2019 revision of the VITA 57.1 standard
    The EEPROM and its complementary components are marked as DNP, as they are not necessary for the ML602 board to function
2024-09-01 Changed clock comparators to dedicated LVDS decoders and changed ADC Vdd inductor to ferrite bead
2024-09-01 Tied PRSNT pin directly to ground without resistor, fixed reference of J1
2024-09-03 Rev 1.1 final version
2024-09-26 Update README.md
    Fixed hyperlink for kicanvas.org
